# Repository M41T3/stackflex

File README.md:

# What is StackFlex?

**StackFlex** is a microcontroller system built around the Espressif ESP32-S3 Mini module. The heart of the system is the **Core PCB**, which houses the microprocessor and supports power delivery via USB or a LiPo battery. Additional functionalities can be seamlessly integrated through modular **Feature PCBs**, which are designed to stack on top of the Core PCB.

The StackFlex system is highly extensible and flexible, all within a compact 40 mm x 40 mm form factor. Leveraging the advanced capabilities of the ESP32-S3 — such as Bluetooth LE, WiFi, and more — the innovative stacking mechanism, and templates for custom Feature PCBs, the system offers virtually unlimited use cases, constrained only by your imagination.

# Contents

- KiCad Projects
- PDF Schematics
- JLCPCB Production Files (Gerber, BOM, CPL)
- StackFlex Arduino Library *[tbd]* 

# Core PCB Highlights

1. **ESP32-S3 Mini 1 Module:** Powerful and energy-efficient microcontroller featuring dual-core processing, integrated WiFi and Bluetooth LE connectivity, AI acceleration, and extensive peripheral support.

2. **3.7 V LiPo:** Power StackFlex using a LiPo battery with state-of-charge (SOC) monitoring.

3. **USB C Connector:** State of the art connector to programm and power the microcontroller and its peripherals.

4. **LiPo Charging:** LiPo charges via USB if it is connected.

5. **Power Monitoring:** Monitor the power consumption and current of stacked Feature PCBs.

6. **GPIO:** Rotationally symmetrical GPIOs for enhanced flexibility.

7. **LEDs:** Two status LEDs (red, green)

=> Detailed documentation [here](/pcb/stackflex_core/).

# Feature PCBs

Feature PCBs enhance the fucntionality of the StackFlex system. Here is a list of already developed Feature PCBs:

- [Air Quality Feature PCB](/pcb/stackflex_feature_air_qual/)
    - Gas Sensor (TVOC, eCO2)
    - Temperature
    - Ambient Light Sensor
    - WS2812B Status LEDs
- more to come..

# Feature PCB Template

Develop and build your own Feature PCB with the provided KiCad Template Project.

=> Detailed documentation [here](/pcb/stackflex_feature_template/).

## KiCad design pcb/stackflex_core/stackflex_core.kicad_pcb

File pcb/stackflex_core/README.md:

# StackFlex Core

**Pinout:** 

**Backside:**

- JST-PH 2mm Connector Footprint for LiPo (check polarity)

**ICs:**
- [ESP32-S3 Mini](https://www.espressif.com/sites/default/files/documentation/esp32-s3-mini-1_mini-1u_datasheet_en.pdf)
- [INA226 Current Sensor](https://www.ti.com/lit/ds/symlink/ina226.pdf)
- [TP4054 Battery Charger](https://www.laskakit.cz/user/related_files/tp4054.pdf)
- [MAX17048 Battery Fuel Gauge](https://www.analog.com/media/en/technical-documentation/data-sheets/MAX17048-MAX17049.pdf)

See schematic for further information.

**Assembly:**

- Pinheader 2x8 2.54 mm
- M3 Spacer

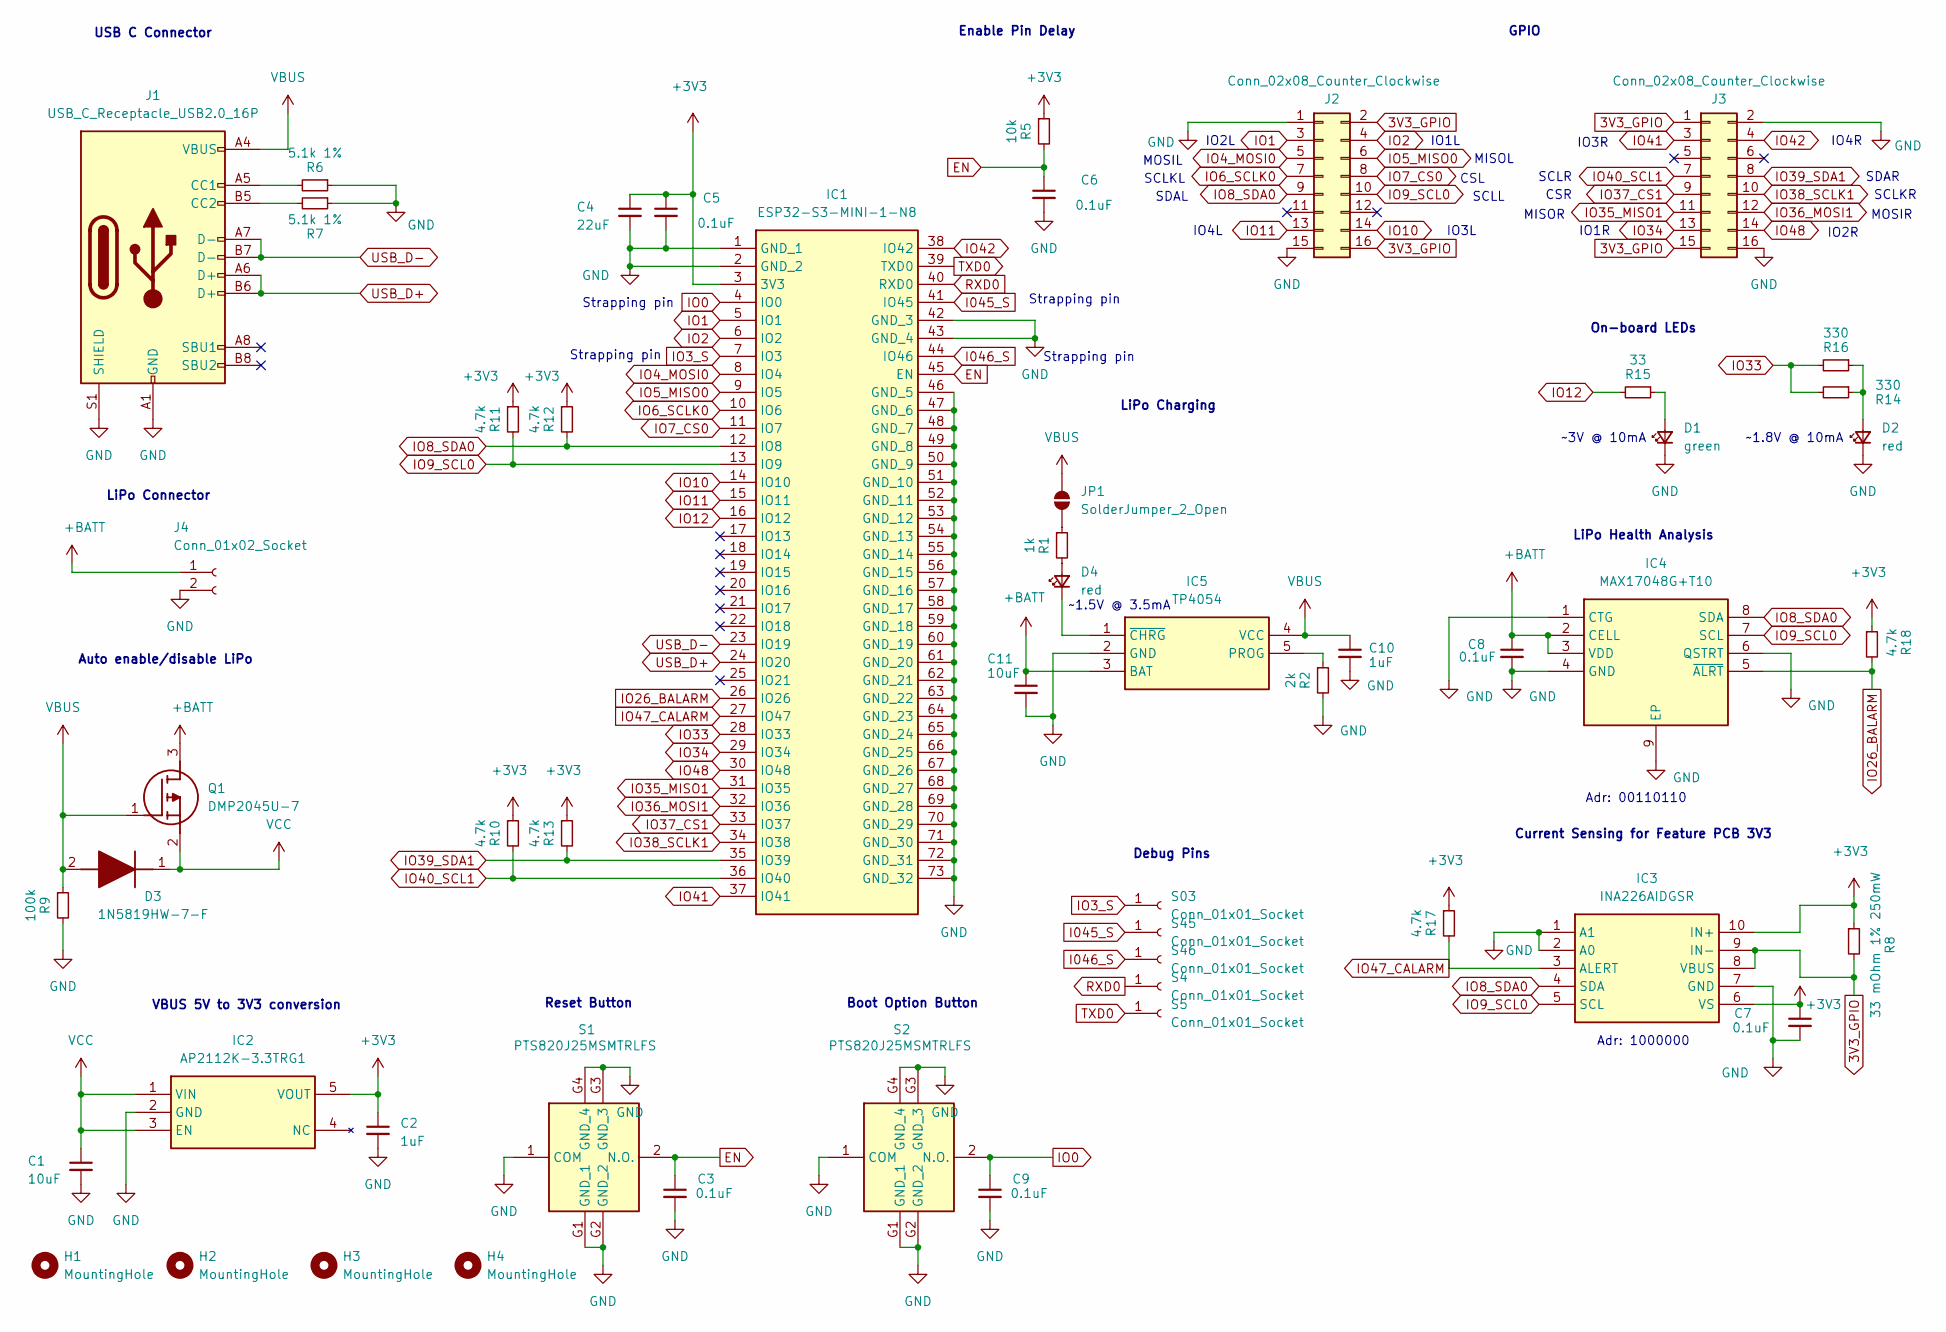
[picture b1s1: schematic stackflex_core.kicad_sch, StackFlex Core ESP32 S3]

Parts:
C1, C11: 10uF; C_0402_1005Metric
C2, C10: 1uF; C_0402_1005Metric
C3, C5, C6, C7, C8, C9: 0.1uF; C_0402_1005Metric
C4: 22uF; C_0603_1608Metric
D1: green; LEDC1005X55N
D2, D4: red; LEDC1005X55N
D3: 1N5819HW-7-F; SOD3716X145N; Mouser Part Number 621-1N5819HW-F
H1, H2, H3, H4: MountingHole; MountingHole_3.2mm_M3_DIN965_Pad
IC1: ESP32-S3-MINI-1-N8; ESP32S3MINI1N8; Mouser Part Number 356-ESP32-S3-MINI1N8
IC2: AP2112K-3.3TRG1; SOT95P285X140-5N; Mouser Part Number 621-AP2112K-3.3TRG1
IC3: INA226AIDGSR; SOP50P490X110-10N; Mouser Part Number 595-INA226AIDGSR
IC4: MAX17048G+T10; SON50P200X200X80-9N-D; Mouser Part Number 700-MAX17048G+T10
IC5: TP4054; SOT95P280X100-5N; Manufacturer_Part_Number TP4054
J1: USB_C_Receptacle_USB2.0_16P; USB_C_Receptacle_GCT_USB4105-xx-A_16P_TopMnt_Horizontal
J2, J3: Conn_02x08_Counter_Clockwise; PinSocket_2x08_P2.54mm_Vertical
J4: Conn_01x02_Socket; JST_PH_S2B-PH-SM4-TB_1x02-1MP_P2.00mm_Horizontal
JP1: SolderJumper_2_Open; SolderJumper-2_P1.3mm_Open_TrianglePad1.0x1.5mm
Q1: DMP2045U-7; SOT96P240X115-3N; Mouser Part Number 621-DMP2045U-7
R1: 1k; R_0402_1005Metric
R2: 2k; R_0402_1005Metric
R5: 10k; R_0402_1005Metric
R6, R7: 5.1k 1%; R_0402_1005Metric
R8: 33 mOhm 1% 250mW; R_0805_2012Metric
R9: 100k; R_0402_1005Metric
R10, R11, R12, R13, R17, R18: 4.7k; R_0402_1005Metric
R14, R16: 330; R_0402_1005Metric
R15: 33; R_0402_1005Metric
S1, S2: PTS820J25MSMTRLFS; Mouser Part Number 611-PTS820J25MSMTR
S03, S4, S5, S45, S46: Conn_01x01_Socket; TestPoint_Pad_D1.0mm

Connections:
3V3_GPIO: IC3.8 (VBUS), IC3.9 (IN-), J2.2, J2.16, J3.1, J3.15, R8.2
+3V3: C2.1, C4.1, C5.1, C7.1, IC1.3 (3V3), IC2.5 (VOUT), IC3.6 (VS), IC3.10 (IN+), R5.1, R8.1, R10.1, R11.1, R12.1, R13.1, R17.1, R18.1
+BATT: C8.1, C11.1, IC4.2 (CELL), IC4.3 (VDD), IC5.3 (BAT), J4.1, Q1.3 (D)
EN: C3.1, C6.1, IC1.45 (EN), R5.2, S1.2 (N.O.)
GND: C1.2, C2.2, C3.2, C4.2, C5.2, C6.2, C7.2, C8.2, C9.2, C10.2, C11.2, D1.1 (K), D2.1 (K), IC1.1 (GND_1), IC1.2 (GND_2), IC1.42 (GND_3), IC1.43 (GND_4), IC1.46 (GND_5), IC1.47 (GND_6), IC1.48 (GND_7), IC1.49 (GND_8), IC1.50 (GND_9), IC1.51 (GND_10), IC1.52 (GND_11), IC1.53 (GND_12), IC1.54 (GND_13), IC1.55 (GND_14), IC1.56 (GND_15), IC1.57 (GND_16), IC1.58 (GND_17), IC1.59 (GND_18), IC1.60 (GND_19), IC1.61 (GND_20), IC1.62 (GND_21), IC1.63 (GND_22), IC1.64 (GND_23), IC1.65 (GND_24), IC1.66 (GND_25), IC1.67 (GND_26), IC1.68 (GND_27), IC1.69 (GND_28), IC1.70 (GND_29), IC1.71 (GND_30), IC1.72 (GND_31), IC1.73 (GND_32), IC2.2 (GND), IC3.1 (A1), IC3.2 (A0), IC3.7 (GND), IC4.1 (CTG), IC4.4 (GND), IC4.6 (QSTRT), IC4.9 (EP), IC5.2 (GND), J1.A1 (GND), J1.A12 (GND), J1.B1 (GND), J1.B12 (GND), J1.S1 (SHIELD), J2.1, J2.15, J3.2, J3.16, J4.2, R2.2, R6.1, R7.1, R9.2, S1.1 (COM), S1.G1 (GND_1), S1.G2 (GND_2), S1.G3 (GND_3), S1.G4 (GND_4), S2.1 (COM), S2.G1 (GND_1), S2.G2 (GND_2), S2.G3 (GND_3), S2.G4 (GND_4)
I045_S: IC1.41 (IO45), S45.1
I046_S: IC1.44 (IO46), S46.1
IO0: C9.1, IC1.4 (IO0), S2.2 (N.O.)
IO1: IC1.5 (IO1), J2.3
IO2: IC1.6 (IO2), J2.4
IO3_S: IC1.7 (IO3), S03.1
IO4_MOSI0: IC1.8 (IO4), J2.5
IO5_MISO0: IC1.9 (IO5), J2.6
IO6_SCLK0: IC1.10 (IO6), J2.7
IO7_CS0: IC1.11 (IO7), J2.8
IO8_SDA0: IC1.12 (IO8), IC3.4 (SDA), IC4.8 (SDA), J2.9, R12.2
IO9_SCL0: IC1.13 (IO9), IC3.5 (SCL), IC4.7 (SCL), J2.10, R11.2
IO10: IC1.14 (IO10), J2.14
IO11: IC1.15 (IO11), J2.13
IO12: IC1.16 (IO12), R15.2
IO26_BALARM: IC1.26 (IO26), IC4.5 (~ALRT), R18.2
IO33: IC1.28 (IO33), R14.2, R16.2
IO34: IC1.29 (IO34), J3.13
IO35_MISO1: IC1.31 (IO35), J3.11
IO36_MOSI1: IC1.32 (IO36), J3.12
IO37_CS1: IC1.33 (IO37), J3.9
IO38_SCLK1: IC1.34 (IO38), J3.10
IO39_SDA1: IC1.35 (IO39), J3.8, R13.2
IO40_SCL1: IC1.36 (IO40), J3.7, R10.2
IO41: IC1.37 (IO41), J3.3
IO42: IC1.38 (IO42), J3.4
IO47_CALARM: IC1.27 (IO47), IC3.3 (ALERT), R17.2
IO48: IC1.30 (IO48), J3.14
unnamed: D1.2 (A), R15.1
unnamed: D2.2 (A), R14.1, R16.1
unnamed: D4.2 (A), R1.2
unnamed: D4.1 (K), IC5.1 (~CHRG)
unnamed: IC5.5 (PROG), R2.1
unnamed: J1.A5 (CC1), R6.2
unnamed: J1.B5 (CC2), R7.2
unnamed: JP1.1 (A), R1.1
RXD0: IC1.40 (RXD0), S4.1
TXD0: IC1.39 (TXD0), S5.1
USB_D+: IC1.24 (IO20), J1.A6 (D+), J1.B6 (D+)
USB_D-: IC1.23 (IO19), J1.A7 (D-), J1.B7 (D-)
VBUS: C10.1, D3.2 (A), IC5.4 (VCC), J1.A4 (VBUS), J1.A9 (VBUS), J1.B4 (VBUS), J1.B9 (VBUS), JP1.2 (B), Q1.1 (G), R9.1
VCC: C1.1, D3.1 (K), IC2.1 (VIN), IC2.3 (EN), Q1.2 (S)

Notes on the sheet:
IO2L
Enable Pin Delay
IO2R
IO1L
~3V @ 10mA
VBUS 5V to 3V3 conversion
IO1R
Strapping pin
Reset Button
USB C Connector
MOSIR
CSL
SCLL
SCLKL
MOSIL
Auto enable/disable LiPo
SCLKR
MISOL
IO3R
IO4L
Adr: 00110110
~1.5V @ 3.5mA
MISOR
Adr: 1000000
LiPo Charging
SDAR
Debug Pins
IO4R
~1.8V @ 10mA
LiPo Health Analysis
LiPo Connector
CSR
IO3L
Current Sensing for Feature PCB 3V3
GPIO
On-board LEDs
SCLR
SDAL
Boot Option Button

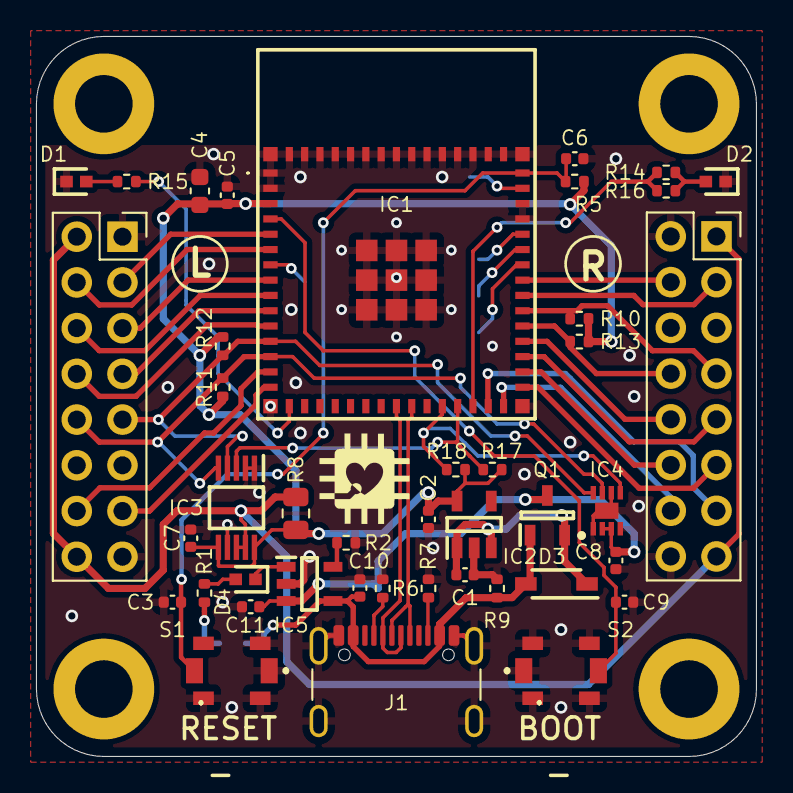
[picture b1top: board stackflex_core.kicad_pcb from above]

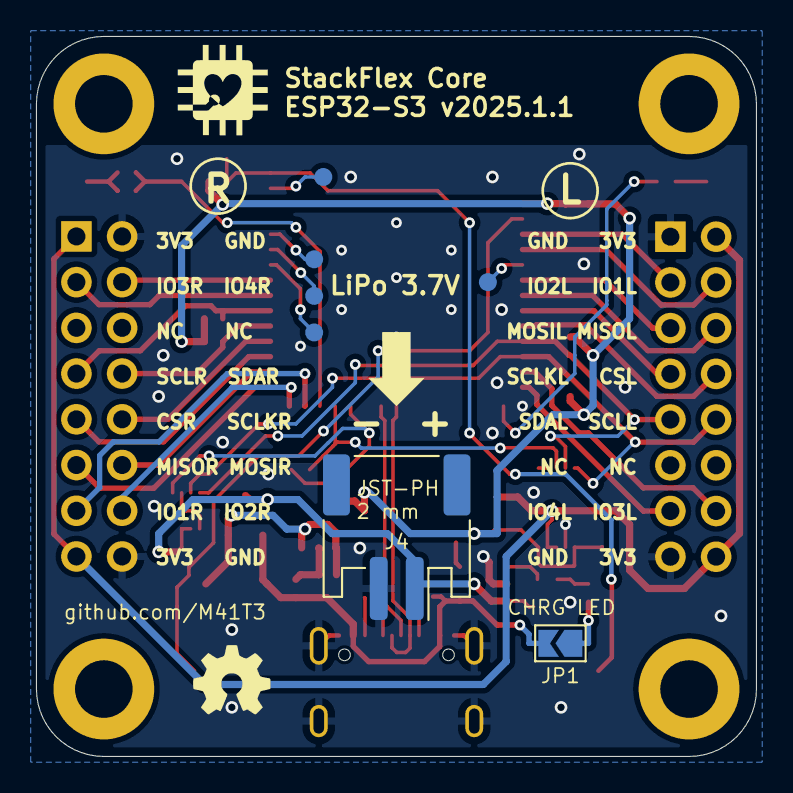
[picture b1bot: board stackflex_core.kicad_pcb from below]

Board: 2 copper layers, 40.0 x 40.0 mm, 53 parts (7 on the bottom side), 47 nets.

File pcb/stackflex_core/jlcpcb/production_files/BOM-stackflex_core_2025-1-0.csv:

Comment,Designator,Footprint,LCSC,Quantity
0.1uF,"C3,C5,C6,C7,C8,C9",C_0402_1005Metric,C1525,6
10uF,C1,C_0402_1005Metric,C15525,1
USB_C_Receptacle_USB2.0_16P,J1,USB_C_Receptacle_GCT_USB4105-xx-A_16P_TopMnt_Horizontal,C165948,1
0,"R1,R2,R3,R4",R_0402_1005Metric,C17168,4
PTS820J25MSMTRLFS,"S1,S2",PTS820J25MSMTRLFS,C221900,2
330,"R14,R16",R_0402_1005Metric,C25104,2
33,R15,R_0402_1005Metric,C25105,1
100k,R9,R_0402_1005Metric,C25741,1
10k,R5,R_0402_1005Metric,C25744,1
4.7k,"R10,R11,R12,R13,R17,R18",R_0402_1005Metric,C25900,6
5.1k 1%,"R6,R7",R_0402_1005Metric,C25905,2
MAX17048G+T10,IC4,SON50P200X200X80-9N-D,C2682616,1
ESP32-S3-MINI-1-N8,IC1,ESP32S3MINI1N8,C2913206,1
DMP2045U-7,Q1,SOT96P240X115-3N,C459541,1
INA226AIDGSR,IC3,SOP50P490X110-10N,C49851,1
AP2112K-3.3TRG1,IC2,SOT95P285X140-5N,C51118,1
1uF,C2,C_0402_1005Metric,C52923,1
22uF,C4,C_0603_1608Metric,C59461,1
green,D1,LEDC1005X55N,C71911,1
red,D2,LEDC1005X55N,C74338,1
1N5819HW-7-F,D3,SOD3716X145N,C82544,1
.01 1% 250mW,R8,RESC2013X45N,C844478,1

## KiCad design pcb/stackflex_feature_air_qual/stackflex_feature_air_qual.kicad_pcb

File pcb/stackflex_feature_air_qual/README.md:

# StackFlex Air Quality Feature PCB

**Sensors**:

- [LM75 Temperature Sensor](https://www.analog.com/media/en/technical-documentation/data-sheets/lm75.pdf)
- [OPT3001 Ambient Light Sensor (ALS)](https://www.ti.com/lit/ds/symlink/opt3001.pdf?ts=1736604398451)
- [SGP30 Indoor Air Quality Sensor](https://sensirion.com/media/documents/984E0DD5/61644B8B/Sensirion_Gas_Sensors_Datasheet_SGP30.pdf)

See schematic for further information.

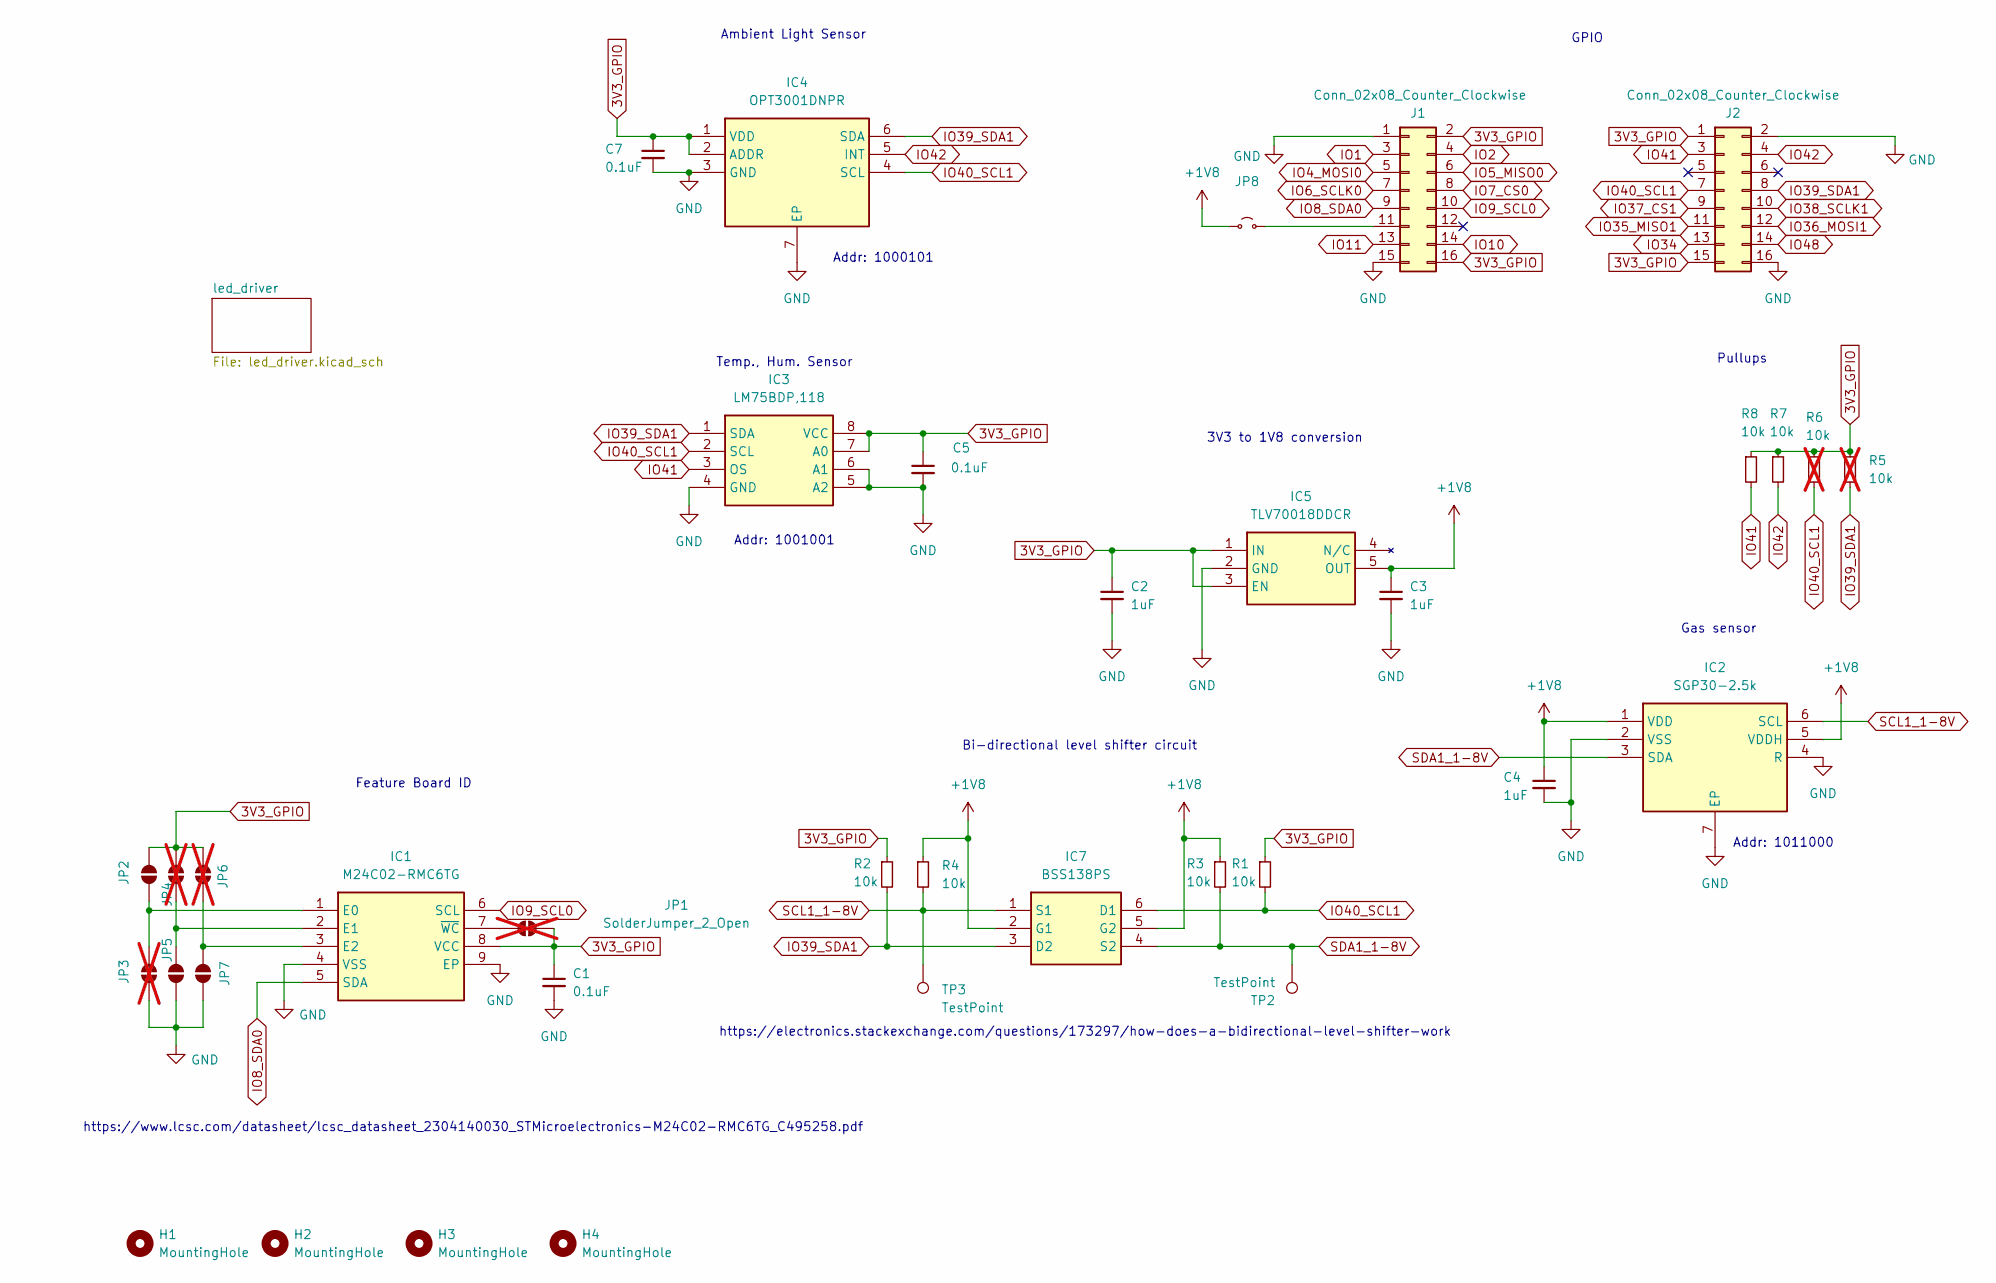
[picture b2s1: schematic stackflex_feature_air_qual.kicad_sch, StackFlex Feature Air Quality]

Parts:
C1, C5, C7: 0.1uF; C_0402_1005Metric
C2, C3, C4: 1uF; C_0402_1005Metric
H1, H2, H3, H4: MountingHole; MountingHole_3.2mm_M3_DIN965_Pad
IC1: M24C02-RMC6TG; M24C16RMC6TG; Mouser Part Number 511-M24C16-RMC6TG
IC2: SGP30-2.5k; SON80P245X245X90-7N; Mouser Part Number 403-SGP30-2.5K
IC3: LM75BDP,118; SOP65P490X110-8N; Mouser Part Number 771-LM75BDP
IC4: OPT3001DNPR; SON65P200X200X65-7N-D; Mouser Part Number 595-OPT3001DNPR
IC5: TLV70018DDCR; SOT95P280X110-5N; Mouser Part Number 595-TLV70018DDCR
IC7: BSS138PS; SOT65P210X110-6N; Mouser Part Number N/A
J1, J2: Conn_02x08_Counter_Clockwise; PinSocket_2x08_P2.54mm_Vertical
JP1, JP3, JP4, JP6: SolderJumper_2_Open; R_0402_1005Metric; not fitted
JP2, JP5, JP7: SolderJumper_2_Open; R_0402_1005Metric
JP8: Jumper_2_Small_Open; SolderJumper-2_P1.3mm_Open_TrianglePad1.0x1.5mm
R1, R2, R3, R4, R7, R8: 10k; R_0402_1005Metric
R5, R6: 10k; R_0402_1005Metric; not fitted
TP2, TP3: TestPoint; TestPoint_Pad_D1.0mm

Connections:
3V3_GPIO: C1.1, C2.1, C5.1, C7.1, IC1.8 (VCC), IC3.7 (A0), IC3.8 (VCC), IC4.1 (VDD), IC4.2 (ADDR), IC5.1 (IN), IC5.3 (EN), J1.2, J1.16, J2.1, J2.15, JP1.2 (B), JP2.2 (B), JP4.2 (B), JP6.2 (B), R1.1, R2.1, R5.1, R6.1, R7.1, R8.1; also elsewhere on the board
+1V8: C3.1, C4.1, IC2.1 (VDD), IC2.5 (VDDH), IC5.5 (OUT), IC7.2 (G1), IC7.5 (G2), JP8.1 (A), R3.1, R4.1
GND: C1.2, C2.2, C3.2, C4.2, C5.2, C7.2, IC1.4 (VSS), IC1.9 (EP), IC2.2 (VSS), IC2.4 (R), IC2.7 (EP), IC3.4 (GND), IC3.5 (A2), IC3.6 (A1), IC4.3 (GND), IC4.7 (EP), IC5.2 (GND), J1.1, J1.15, J2.2, J2.16, JP3.1 (A), JP5.1 (A), JP7.1 (A); also elsewhere on the board
IO1: J1.3
IO2: J1.4
IO4_MOSI0: J1.5
IO5_MISO0: J1.6
IO6_SCLK0: J1.7
IO7_CS0: J1.8
IO8_SDA0: IC1.5 (SDA), J1.9
IO9_SCL0: IC1.6 (SCL), J1.10
IO10: J1.14
IO11: J1.13
IO34: J2.13; also elsewhere on the board
IO35_MISO1: J2.11
IO36_MOSI1: J2.12
IO37_CS1: J2.9
IO38_SCLK1: J2.10
IO39_SDA1: IC3.1 (SDA), IC4.6 (SDA), IC7.3 (D2), J2.8, R2.2, R5.2
IO40_SCL1: IC3.2 (SCL), IC4.4 (SCL), IC7.6 (D1), J2.7, R1.2, R6.2
IO41: IC3.3 (OS), J2.3, R8.2
IO42: IC4.5 (INT), J2.4, R7.2
IO48: J2.14; also elsewhere on the board
unnamed: IC1.1 (E0), JP2.1 (A), JP3.2 (B)
unnamed: IC1.2 (E1), JP4.1 (A), JP5.2 (B)
unnamed: IC1.3 (E2), JP6.1 (A), JP7.2 (B)
unnamed: IC1.7 (~WC), JP1.1 (A)
unnamed: J1.11, JP8.2 (B)
SCL1_1-8V: IC2.6 (SCL), IC7.1 (S1), R4.2, TP3.1
SDA1_1-8V: IC2.3 (SDA), IC7.4 (S2), R3.2, TP2.1

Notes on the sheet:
Addr: 1001001
Temp., Hum. Sensor
GPIO
Addr: 1000101
Bi-directional level shifter circuit
3V3 to 1V8 conversion
Gas sensor
Feature Board ID
https://www.lcsc.com/datasheet/lcsc_datasheet_2304140030_STMicroelectronics-M24C02-RMC6TG_C495258.pdf
Pullups
Addr: 1011000
https://electronics.stackexchange.com/questions/173297/how-does-a-bidirectional-level-shifter-work
Ambient Light Sensor

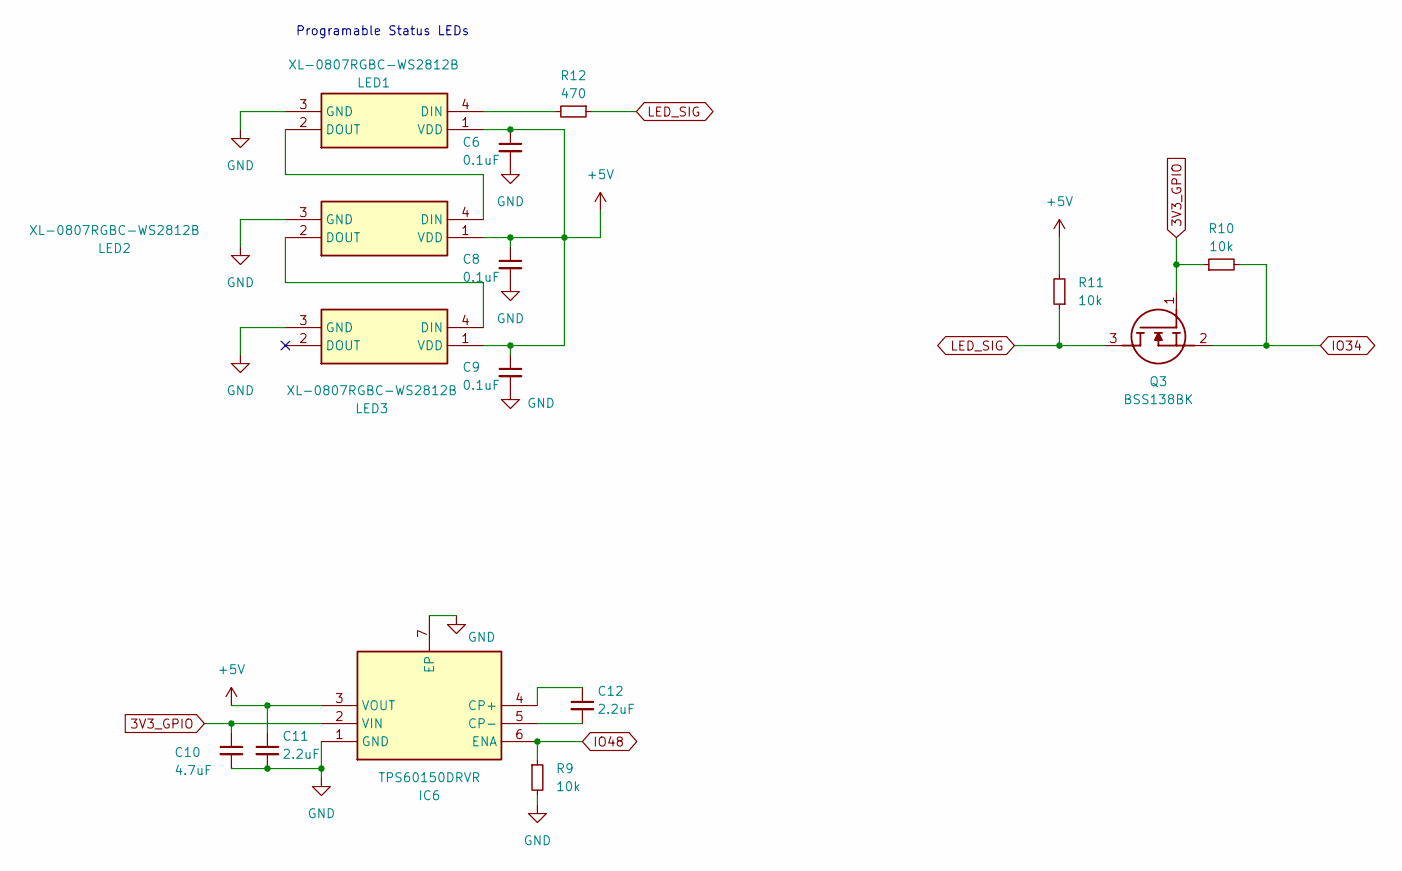
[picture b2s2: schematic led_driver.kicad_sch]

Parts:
C6, C8, C9: 0.1uF; C_0402_1005Metric
C10: 4.7uF; C_0402_1005Metric
C11, C12: 2.2uF; C_0402_1005Metric
IC6: TPS60150DRVR; SON65P200X200X80-7N; Mouser Part Number 595-TPS60150DRVR
LED1, LED2, LED3: XL-0807RGBC-WS2812B; XL0807RGBCWS2812B; Manufacturer_Part_Number XL-0807RGBC-WS2812B
Q3: BSS138BK; TL431CDBZR215; Mouser Part Number N/A
R9, R10, R11: 10k; R_0402_1005Metric
R12: 470; R_0402_1005Metric

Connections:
3V3_GPIO: C10.1, IC6.2 (VIN), Q3.1 (G), R10.1; also elsewhere on the board
+5V: C6.1, C8.1, C9.1, C11.1, IC6.3 (VOUT), LED1.1 (VDD), LED2.1 (VDD), LED3.1 (VDD), R11.2
GND: C6.2, C8.2, C9.2, C10.2, C11.2, IC6.1 (GND), IC6.7 (EP), LED1.3 (GND), LED2.3 (GND), LED3.3 (GND), R9.2; also elsewhere on the board
IO34: Q3.2 (S), R10.2; also elsewhere on the board
IO48: IC6.6 (ENA), R9.1; also elsewhere on the board
LED_SIG: Q3.3 (D), R11.1, R12.1
unnamed: C12.1, IC6.4 (CP+)
unnamed: C12.2, IC6.5 (CP-)
unnamed: LED1.4 (DIN), R12.2
unnamed: LED1.2 (DOUT), LED2.4 (DIN)
unnamed: LED2.2 (DOUT), LED3.4 (DIN)

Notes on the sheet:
Programable Status LEDs

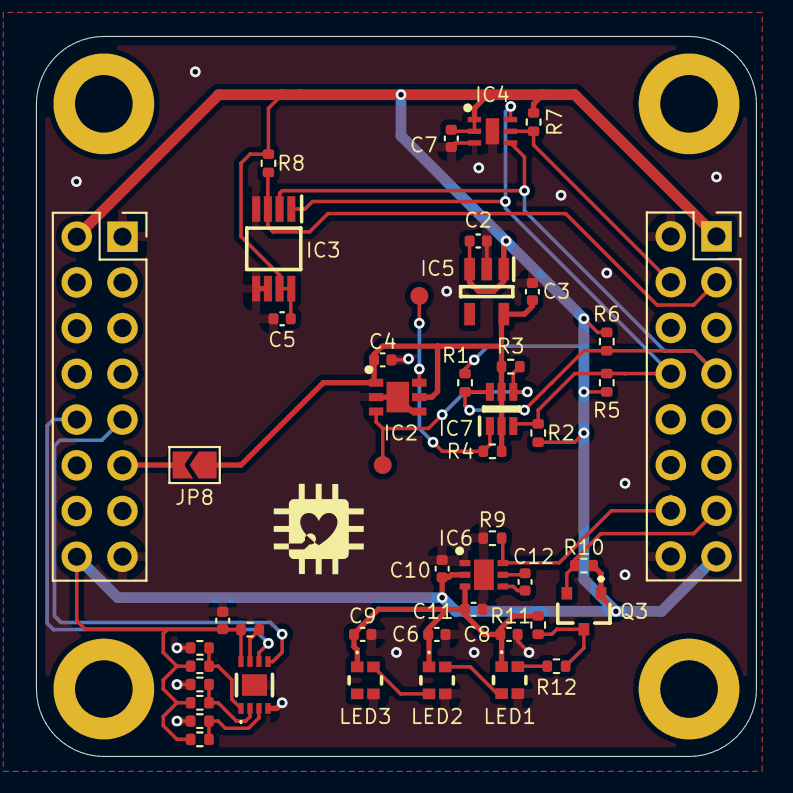
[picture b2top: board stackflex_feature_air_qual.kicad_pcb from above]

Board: 2 copper layers, 40.0 x 40.0 mm, 51 parts (0 on the bottom side), 25 nets.

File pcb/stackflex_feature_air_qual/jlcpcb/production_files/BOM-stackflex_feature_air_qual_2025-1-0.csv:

Comment,Designator,Footprint,LCSC,Quantity
BSS138BK,Q3,TL431CDBZR215,C112239,1
2.2uF,"C11,C12",C_0402_1005Metric,C12530,2
0.1uF,"C1,C5,C6,C7,C8,C9",C_0402_1005Metric,C1525,6
SolderJumper_2_Open,"JP2,JP5,JP7",R_0402_1005Metric,C17168,3
TPS60150DRVR,IC6,SON65P200X200X80-7N,C182429,1
BSS138PS,IC7,SOT65P210X110-6N,C193381,1
4.7uF,C10,C_0402_1005Metric,C23733,1
470,R12,R_0402_1005Metric,C25117,1
10k,"R1,R10,R11,R2,R3,R4,R7,R8,R9",R_0402_1005Metric,C25744,9
"LM75BDP,118",IC3,SOP65P490X110-8N,C33099,1
XL-0807RGBC-WS2812B,"LED1,LED2,LED3",XL0807RGBCWS2812B,C3646929,3
M24C02-RMC6TG,IC1,M24C16RMC6TG,C495258,1
SGP30-2.5k,IC2,SON80P245X245X90-7N,C514454,1
1uF,"C2,C3,C4",C_0402_1005Metric,C52923,3
TLV70018DDCR,IC5,SOT95P280X110-5N,C79924,1
OPT3001DNPR,IC4,SON65P200X200X65-7N-D,C90462,1

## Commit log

2024-12-29 core 2025.1.1 and air quality 2025.1.0
2025-01-11 add docu for v1.1
2025-01-11 readme fix
